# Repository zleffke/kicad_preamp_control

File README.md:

# kicad_preamp_control
Control circuit for coax relay, transfer switch, and preamp control.  Used in VTGS S-Band ground station RF Front End, but could also be used for EME or other applications.

## Component Description
The major components of the RF front end preamplifier includes a fail safe coax relay, a failsafe coax transfer switch, and a Low Noise Amplifier (LNA).  The actual components used are listed below:
- Coax Relay: [Relcomm RDS-2S1A6](https://rfrelaystore.com/product/rds-2s1a6/)
- Transfer Switch: [Relcomm RTS-TS1A6](https://rfrelaystore.com/product/rts-ts1a6/)
- LNA: [Kuhne Electronics KU LNA 220240 A](https://www.kuhne-electronic.com/funk/en/shop/industrial/prof-low-noise-ampli/prof-lna-s-band/KU+LNA+220240+A++Super+Low+Noise+Amplifier/?card=1794)

Since the coax relay and transfer switch are of the 'FAILSAFE' design, when de-energized they are in their Normally Closed positions and when energized they are in their Normally Open position.  Note that in the VTGS system, two front end preamplifier subsystems are utilized, one per polarization (LHCP or RHCP).

## Signal Flow and State Overview
The default (unpowered) state of the preamplifier subsystem is BYPASS, which routes the antenna signal around the unpowered LNA via the Normally Closed paths of the relay and transfer switch.  The system can also be placed in the RECEIVE (RX) state which energizes the coax relay and transfer switch (placing them in their Normally Open positions) and routes the signal through the powered on LNA (+12VDC provided by the board). A third state is the TERMINATE state which only powers up the transfer switch and routes the ANTENNA port to a 50 ohm termination, which may be desirable if only using a single polarization.  The figure below shows the states of the system. 

## Control Circuit Description
The coax relay and transfer switch operates at 28 V and the LNA operates from a 12V source.  This control board circuit is powered from a 28V supply.  The control circuitry is based on a FET switch.  Nominal operation assumes a 28V source supplied to the system, and then control via grounding of the appropriate control line for the desired operating state.  These control signals include RX_EN, RX_PTT (for sequencing), and TERM.  

The LNA used in this design is the [Kuhne Electronics KU LNA 220240 A](https://www.kuhne-electronic.com/funk/en/shop/industrial/prof-low-noise-ampli/prof-lna-s-band/KU+LNA+220240+A++Super+Low+Noise+Amplifier/?card=1794). An integrated 12V regulator drops the voltage down to the 12V range required for the LNA operation.  For this first version, the power is toggled at the input to a simple LM7812 style voltage regulator.....more detailed examination of this circuit might be investigated in future versions for enable/disable features and noise reduction.  A key feature needed is fast switching, including LNA power down in the PTT process....so the decay time to 0V in the LNA should be very fast, which might not be achievable with the simple 7812 style regulator.  Whenever the SPST Coax Relay is energized, +12VDC will also be applied to the LNA.  

See below for a wiring diagram for connecting the V1, REV- board to the RF components.  A generic 5 pin connector for control is assumed.

### Jumper Settings - V1, REV- Board
For the Version 1, Revision- control board there are three solder jumpers.  Manipulation of the jumper settings allows control of the default states of the system.  Be wary of STATE conflicts if manipulating jumper settings.

#### JP1
JP1 is connected to the RX_EN signal.  The default position of this solder jumper is in a connection to GROUND via a small pcb trace, thus permanently grounding the active low RX_EN signal.  Thus when +28VDC is applied to the control board, the system automatically switches into the RECEIVE state with the RF signal routed through the energized LNA.  If The RX_PTT signal is grounded, the system will switch into the BYPASS state, with power removed from all devices.  Depending on the controller used (sequencer) this default state may not be desirable.  The connection to ground for the RX_EN switch can be removed by cutting the trace between ground and the center terminal of the jumper.  The center pad of JP1 can then be connected (via solder jumper) to the external RX_EN pad for routing off board to a controller that maintains control of the RX_EN signal.

#### JP2 / JP3
Solder Jumpers JP2 and JP3 control the TERM signal routing.  Default state simply routes the signal offboard for external control of the line.  Review the schematic for options for signal routing.  If JP3 is connected to GROUND (2-3) and JP2 routed to its alternative position (2-3), then system will automatically engage the TERM state and the signal currently labelled TERM (active low ENABLES the terminate state) will become something more like TERM_DISABLE (active low will DISABLE the TERM state).  Again, be wary of potential state conflicts if manipulating the default jumper positions.

### Potential State Conflicts
The only major potential conflict to be wary of is energizing both TERM and RX_EN.  Essentially the key thing to remember is that if RX_EN and TERM are both grounded, the system will be placed in the RECEIVE State and the transfer switch will be engaged.  Basically, the RX_EN signal 'supercedes' the TERM signal.  However, if both RX_EN and TERM signals are engaged (remember active low, so both grounded) and then the RX_PTT signal is engaged (again active low), the system will then be placed in the TERM state, NOT the BYPASS state.  This is because the RX_PTT signal disables the power supplied to the Coax Relay and the LNA but NOT the transfer switch.  Thus if the TERM signal is engaged and the transfer switch is energized, The RX_PTT switch WILL NOT remove power from the transfer switch.  Future revisions may address this.

## Credit where its due:
The coax relays in this design are controlled by a [High Current DC Switch](https://www.w6pql.com/high_current_solid-state_dc_switch.htm) based on the W6PQL design.  This gives enable/disable features that are fast acting for minimum PTT switching time (limited by coax relay switching speeds).  Major differences include using a much smaller capacity N-Channel MOSFET for the main switching transistor as we do not need such high current carrying capacity as the original design.

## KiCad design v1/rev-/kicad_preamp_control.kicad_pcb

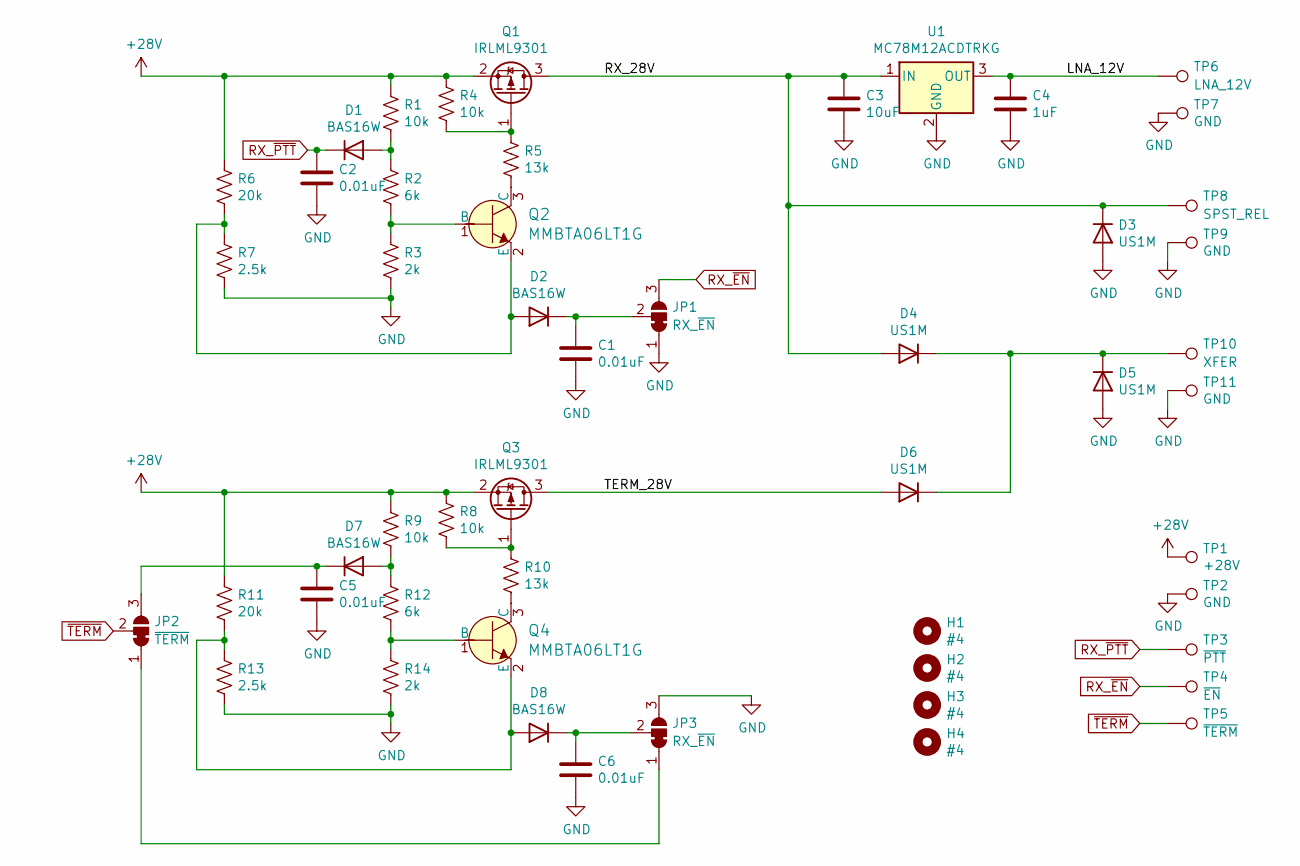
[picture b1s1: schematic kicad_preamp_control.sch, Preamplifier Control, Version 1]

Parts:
C1, C2, C5, C6: 0.01uF; 0805
C3: 10uF; 0805
C4: 1uF; 0805
D1, D2, D7, D8: BAS16W; SOT-323_SC-70
D3, D4, D5, D6: US1M; D_SMA
H1, H2, H3, H4: #4; MountingHole_3.2mm_M3
JP1, JP3: RX_~EN; SolderJumper-3_P1.3mm_Bridged12_RoundedPad1.0x1.5mm_NumberL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
JP2: ~TERM; SolderJumper-3_P1.3mm_Bridged12_RoundedPad1.0x1.5mm_NumberL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
Q1, Q3: IRLML9301; SOT-23-3
Q2, Q4: MMBTA06LT1G; SOT-23-3; MPN MMBTA06LT1G; Digi-Key_PN MMBTA06LT1GOSCT-ND
R1, R4, R8, R9: 10k; 0805
R2, R12: 6k; 0805
R3, R14: 2k; 0805
R5, R10: 13k; 0805
R6, R11: 20k; 0805
R7, R13: 2.5k; 0805
TP1: +28V; TestPoint_Pad_4.0x4.0mm
TP2, TP7, TP9, TP11: GND; TestPoint_Pad_4.0x4.0mm
TP3: ~PTT; TestPoint_Pad_4.0x4.0mm
TP4: ~EN; TestPoint_Pad_4.0x4.0mm
TP5: ~TERM; TestPoint_Pad_4.0x4.0mm
TP6: LNA_12V; TestPoint_Pad_4.0x4.0mm
TP8: SPST_REL; TestPoint_Pad_4.0x4.0mm
TP10: XFER; TestPoint_Pad_4.0x4.0mm
U1: MC78M12ACDTRKG; TO-252-2

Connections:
+28V: Q1.2 (S), Q3.2 (S), R1.1, R4.1, R6.1, R8.1, R9.1, R11.1, TP1.1
/LNA_12V: C4.1, TP6.1, U1.3 (OUT)
/RX_28V: C3.1, D3.1 (K), D4.2 (A), Q1.3 (D), TP8.1, U1.1 (IN)
/TERM_28V: D6.2 (A), Q3.3 (D)
GND: C1.2, C2.2, C3.2, C4.2, C5.2, C6.2, D3.2 (A), D5.2 (A), JP1.1 (A), JP3.3 (B), R3.2, R7.2, R13.2, R14.2, TP2.1, TP7.1, TP9.1, TP11.1, U1.2 (GND)
unnamed: C1.1, D2.3 (K), JP1.2 (C)
unnamed: C5.1, D7.3 (K), JP2.3 (B)
unnamed: C6.1, D8.3 (K), JP3.2 (C)
unnamed: D1.1 (A), R1.2, R2.1
unnamed: D2.1 (A), Q2.2 (E), R6.2, R7.1
unnamed: D4.1 (K), D5.1 (K), D6.1 (K), TP10.1
unnamed: D7.1 (A), R9.2, R12.1
unnamed: D8.1 (A), Q4.2 (E), R11.2, R13.1
unnamed: JP2.1 (A), JP3.1 (A)
unnamed: Q1.1 (G), R4.2, R5.1
unnamed: Q2.1 (B), R2.2, R3.1
unnamed: Q2.3 (C), R5.2
unnamed: Q3.1 (G), R8.2, R10.1
unnamed: Q4.1 (B), R12.2, R14.1
unnamed: Q4.3 (C), R10.2
RX_~EN: JP1.3 (B), TP4.1
RX_~PTT: C2.1, D1.3 (K), TP3.1
~TERM: JP2.2 (C), TP5.1

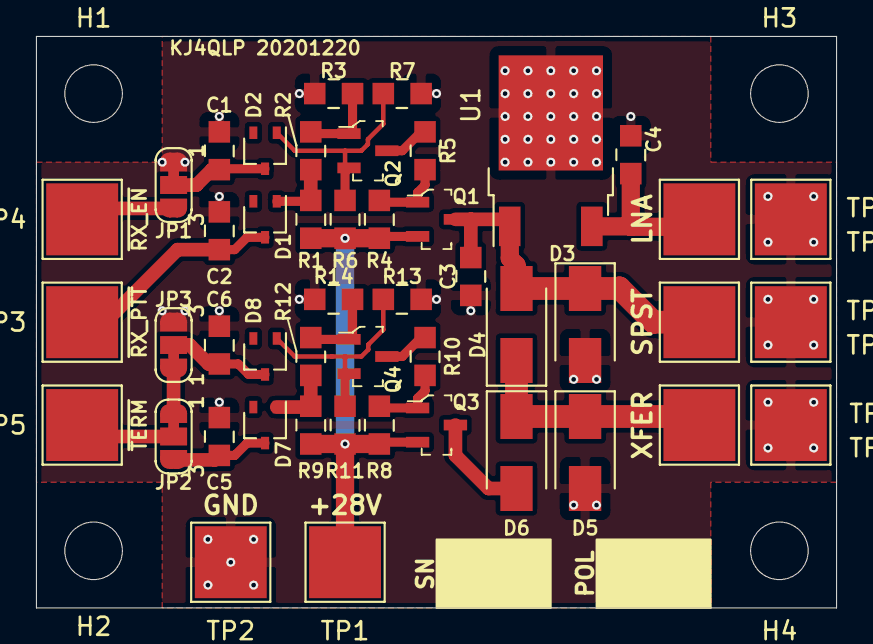
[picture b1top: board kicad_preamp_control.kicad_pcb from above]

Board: 2 copper layers, 44.4 x 31.8 mm, 51 parts (0 on the bottom side), 23 nets.

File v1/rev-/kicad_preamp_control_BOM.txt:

"Source:","/home/zleffke/github/zleffke/kicad/kicad_preamp_control/v1/rev-/kicad_preamp_control.sch"
"Date:","Tue 29 Dec 2020 08:32:07 PM EST"
"Tool:","Eeschema 5.1.6-c6e7f7d~87~ubuntu16.04.1"
"Generator:","/usr/share/kicad/plugins/bom_csv_grouped_by_value_with_fp.py"
"Component Count:","51"
"Ref","Qnty","Value","Cmp name","Footprint","Description","Vendor"
"C1, C2, C5, C6, ","4","0.01uF","C","digikey-footprints:0805","Unpolarized capacitor",""
"C3, ","1","10uF","C","digikey-footprints:0805","Unpolarized capacitor",""
"C4, ","1","1uF","C","digikey-footprints:0805","Unpolarized capacitor",""
"D1, D2, D7, D8, ","4","BAS16W","BAS16W","Package_TO_SOT_SMD:SOT-323_SC-70","100V, 0.175A, High-speed Switching Diode, SOT-323",""
"D3, D4, D5, D6, ","4","US1M","US1M","Diode_SMD:D_SMA","1000V, 1A, General Purpose Rectifier Diode, SMA(DO-214AC)",""
"H1, H2, H3, H4, ","4","#4","MountingHole","MountingHole:MountingHole_3.2mm_M3","Mounting Hole without connection",""
"JP1, JP3, ","2","RX_~EN","SolderJumper_3_Bridged12","Jumper:SolderJumper-3_P1.3mm_Bridged12_RoundedPad1.0x1.5mm_NumberLabels","3-pole Solder Jumper, pins 1+2 closed/bridged",""
"JP2, ","1","~TERM","SolderJumper_3_Bridged12","Jumper:SolderJumper-3_P1.3mm_Bridged12_RoundedPad1.0x1.5mm_NumberLabels","3-pole Solder Jumper, pins 1+2 closed/bridged",""
"Q1, Q3, ","2","IRLML9301","IRLML9301","digikey-footprints:SOT-23-3","-3.6A Id, -30V Vds, P-Channel HEXFET Power MOSFET, 64mOhm Rds, SOT-23",""
"Q2, Q4, ","2","MMBTA06LT1G","MMBTA06LT1G","digikey-footprints:SOT-23-3","TRANS NPN 80V 0.5A SOT23",""
"R1, R4, R8, R9, ","4","10k","R_US","digikey-footprints:0805","Resistor, US symbol",""
"R2, R12, ","2","6k","R_US","digikey-footprints:0805","Resistor, US symbol",""
"R3, R14, ","2","2k","R_US","digikey-footprints:0805","Resistor, US symbol",""
"R5, R10, ","2","13k","R_US","digikey-footprints:0805","Resistor, US symbol",""
"R6, R11, ","2","20k","R_US","digikey-footprints:0805","Resistor, US symbol",""
"R7, R13, ","2","2.5k","R_US","digikey-footprints:0805","Resistor, US symbol",""
"TP1, ","1","+28V","TestPoint","TestPoint:TestPoint_Pad_4.0x4.0mm","test point",""
"TP2, TP7, TP9, TP11, ","4","GND","TestPoint","TestPoint:TestPoint_Pad_4.0x4.0mm","test point",""
"TP3, ","1","~PTT","TestPoint","TestPoint:TestPoint_Pad_4.0x4.0mm","test point",""
"TP4, ","1","~EN","TestPoint","TestPoint:TestPoint_Pad_4.0x4.0mm","test point",""
"TP5, ","1","~TERM","TestPoint","TestPoint:TestPoint_Pad_4.0x4.0mm","test point",""
"TP6, ","1","LNA_12V","TestPoint","TestPoint:TestPoint_Pad_4.0x4.0mm","test point",""
"TP8, ","1","SPST_REL","TestPoint","TestPoint:TestPoint_Pad_4.0x4.0mm","test point",""
"TP10, ","1","XFER","TestPoint","TestPoint:TestPoint_Pad_4.0x4.0mm","test point",""
"U1, ","1","MC78M12ACDTRKG","L7812","Package_TO_SOT_SMD:TO-252-2","Positive 1.5A 35V Linear Regulator, Fixed Output 12V, TO-220/TO-263/TO-252",""

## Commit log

2020-12-30 first version of schematic and pcb. This commit submitted to osh park.
2020-12-30 added BOM
2021-01-01 adding some figures

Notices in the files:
v1/rev-/kicad_preamp_control.sch:
creativecommons.org/licenses/by/4.0
License: CC BY 4.0
